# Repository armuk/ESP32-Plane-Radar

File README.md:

# Plane Radar

A live **ADS-B radar** on a round display: aircraft around your location with routes, aircraft details, local weather and time, settings in the browser, and signed over-the-air updates.

**Firmware:** [Releases](../../releases) · **3D printed case (STL + assembly):** [MakerWorld](https://makerworld.com/en/models/2872376-esp32-plane-radar-live-ads-b-on-a-round-display#profileId-3207083)

## Boards

Each board has its own folder, build and releases. **Flash only the files for your board.**

| Folder | Board | Status | Release tags and files |
|--------|-------|--------|------------------------|
| [`firmware/c3-supermini`](firmware/c3-supermini) | ESP32-C3 Super Mini + 1.28″ round GC9A01 (240×240) | **Released** | `v2.2.1`; files `plane-radar-v2.2.1-…`. These are the releases marked **Latest**. |
| [`firmware/s3`](firmware/s3) | ESP32-S3 with PSRAM (board to be chosen) | Port in progress, not usable yet | Will be `s3-v0.1.0`; files `plane-radar-s3-v0.1.0-…` |
| [`firmware/p4`](firmware/p4) | ESP32-P4 4″ round 720×720 touch (Waveshare ESP32-P4-WIFI6-Touch-LCD-4C) | Port in progress, not usable yet | Will be `p4-v0.1.0`; files `plane-radar-p4-v0.1.0-…` |
| [`firmware/cm4`](firmware/cm4) | Raspberry Pi CM4 or CM5 in an Echo Show 5 (2nd gen) case, 5.5″ 960×480 touch: radar plus Home Assistant dashboard | Hardware research, not usable yet | To be decided (not an ESP32 image) |

If you have a radar today, it is the **C3 Super Mini**: see its [README](firmware/c3-supermini/README.md) for wiring, setup, flashing and updates.

A file for a different chip (C3, S3 or P4) is refused: esptool, web flashers and the radar's own update all check the chip type. Before the S3 and P4 are released, their images will also carry a board marker, so a file for another board with the same chip is refused too. USB flashing the right file always recovers a radar.

## Building

Each folder is a separate PlatformIO project:

```bash
cd firmware/c3-supermini && pio run -e supermini
cd firmware/s3 && pio run -e s3
cd firmware/p4 && pio run -e p4
```

The S3 and P4 folders started as copies of the C3 firmware; their READMEs list what each port still needs. The [Build workflow](.github/workflows/build.yml) tests, checks and builds every board on each push; the [Release workflow](.github/workflows/release.yml) releases the C3 Super Mini from `v*` tags.

## Security, credits and licence

- [SECURITY.md](SECURITY.md): support period, reporting a vulnerability, network interfaces and the update signing key (written for the C3 Super Mini; the other boards will follow it).
- Origins and credits: this project builds on [ironicbadger/ESP32-Plane-Radar](https://github.com/ironicbadger/ESP32-Plane-Radar), a fork of [MatixYo/ESP32-Plane-Radar](https://github.com/MatixYo/ESP32-Plane-Radar). See the C3 README's [Origins and credits](firmware/c3-supermini/README.md#origins-and-credits).
- [LICENSE](LICENSE) (MIT).

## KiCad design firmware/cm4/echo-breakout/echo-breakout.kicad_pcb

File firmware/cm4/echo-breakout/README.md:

# Echo Show 5 breakout board (v2, drop-in)

A test board **the size and shape of the Echo's mainboard** (KC19-TI MLB, 108 × 60 mm). It screws into
the rear case in the mainboard's place, so every original ribbon plugs straight in. It's for mapping and
testing the Echo Show 5 (2nd gen, "cronos") parts before the CM4 carrier board is designed. See
[ECHO-SHOW-5.md](../ECHO-SHOW-5.md) for the hardware findings it serves.

## Why it's mainboard-shaped

The ribbons are short:

| Ribbon | Length | Note |
|---|---|---|
| Display (J44) | 17.5 mm | Tight |
| Touch (J30) | About 17.5 mm | Tight |
| Top board (J100) | 23 mm | |
| IO board (J46) | 44 mm | |

None of them can reach a board placed beside the Echo. So each socket sits where the original does, with
its ribbon-facing edge at the original's position. To work with the board outside the case, use the
[ribbon extenders](../ribbon-extenders/README.md). The positions were measured from two photos
(±0.3 mm across, ±0.8 mm down; see "Positions from the photos" in ECHO-SHOW-5.md).

## What's on it

| Socket | Part (LCSC) | Position (mm from the top-left corner) | Broken out to |
|---|---|---|---|
| **J44** display | Hirose FH26W-33S-0.3SHW(60) (C424654) | Body edge x = 4.2, centred y = 39.0, lock side left | P1, 2 × 17 |
| **J30** touch | Hirose FH34SRJ-8S-0.5SH(50) (C88372) | Front face x = 15.1, centred y = 53.8, opening left | P4, 1 × 8 |
| **J100** top board | HCTL HC-FPC-03-10-23RLTAG (C3012331), a copy of Hirose's FH26W-23S-0.3SHW | Body edge y = 4.5, centred x = 22.4, lock side up | P3, 2 × 12 |
| **J46** IO board | Hirose FH26W-31S-0.3SHW(60) (C2973806) | Body edge y = 4.4, centred x = 42.0, lock side up | P2, 2 × 16 |
| **J2** speaker | Molex Pico-SPOX 87438-0243 (C240853) | Centred x = 82.0, mating face 0.6 mm from the top edge, as on the mainboard | P8, 1 × 2 (top-right corner) |

How to read the headers:
- **Header pin n = Echo pin n** on every header, using the mainboard's own silkscreen pin 1:
  - J44 and J30: top end. On J30, 8 is at the bottom, nearest screw S4.
  - J100 and J46: right-hand end.
- The 2-row headers (J44, J100, J46) end with an extra GND pin.

**Mounting:**
- Six 2.6 mm plated holes at the original screw positions, assumed M2. The positions were measured
  from ruler photos of the mainboard (see "Measuring the screw holes" below). An M2 screw can sit up to
  0.3 mm off-centre in a 2.6 mm hole, and the screw head still covers it (the Echo's screws have 3.5 mm heads and are 5.1 mm long).
- **Each hole sits in an exposed, grounded copper pad** on both faces, as on the mainboard: 4.8 mm
  across (3.6 mm at S4, where the board edge is close). The screw head bears on the pad, not on
  solder mask, and the screw ties the board's ground to the case post.
- No tracks or vias within 2.6 mm of any hole centre on the outer layers (rule areas `SCREW_H1`–`H6`).
  The head reaches 1.9 mm out, or 2.2 mm with the screw fully off-centre.
- Screw S4 (bottom edge) is only 2.1 mm from the edge.
- **J44, J46 and J100 are Hirose FH26W sockets, the same way round as the mainboard's.** The ribbon
  enters on the lock side, which faces the board edge. Lift the lock, lay the ribbon in with its contacts
  as it sat in the Echo, and press the lock down onto it. The mainboard's J46 carries Hirose's mark on
  its lock and matches the FH26W-31 in size, leg counts (16 at the edge, 15 inboard) and end tabs.
- **J30 is a Hirose FH34SRJ-8S-0.5SH, at the mainboard socket's own position.** The mainboard's
  socket matches that part on every measured point: 6.0 mm wide, 3.8 mm deep, back-flip lock on the leg
  side, 0.3 mm ribbon, and a ribbon with 1.5 mm of bare contact and its insertion line at 1.5 mm.
  - An FH12 (used in earlier versions) doesn't work: it needs the ribbon 4.4 mm deep, and the Echo's
    touch ribbon has a 3 mm tongue of which 1.5 mm goes in.
  - The footprint is built in `gen_board.py` from Hirose's recommended pattern (FH34 catalogue, page 8,
    in `../parts-documentation/`): eight 0.3 × 0.8 mm lands and two 0.4 × 0.8 mm fitting lands.
  - **It's a back-flip socket: the lock lifts on the leg side, away from the ribbon.** Push the ribbon
    in to its white line, then press the lock down.
- **Bare ground pads.** The mainboard grounds to its surroundings through bare gold pads, and the
  breakout has the same ones. Keep them all bare: no tape, no flux residue.
  - **GP1, top, left of J30** (x 1.0–11.5, y 46.0–59.0): the touch ribbon lies across it. Four plated
    holes tie it to the ground pours on every layer.
  - **GP2, top-left corner** (x 0.6–9.0, y 0.6–4.8, with a sliver down the display edge to a second
    patch at y 12.4–14.0): the metal-mesh tape from the button/mic board sticks here.
  - **GB1–GB9, back:** nine pads where the display frame's conductive fabric gaskets press (GB2–GB5,
    GB7–GB9), plus GB1 under the J30 corner, where the GT911's ground pad rests, and GB6 on the
    display edge. No through-hole part sits inside any of them. Positions are in `BACK_PADS` in
    `gen_board.py`.
- **Two 2.5 mm alignment holes**, as on the mainboard, for the case's 1.8–1.9 mm locating pegs: A1 at 3.1, 16.8 (by the original's J45)
  and A2 at 93.4, 17.05 (by the original's part-number print). The mainboard's are about 2.5 mm.

**ESP32 section** (for the touch test, and for buttons, LEDs and ADC readings later):

- **U1A/U1B:** two 1 × 8 female sockets, 15.24 mm (0.6″) apart, for an **ESP32-C3 SuperMini**,
  component side up, with its USB-C pointing **left, into the board**. The case wall is too close to the
  right and bottom edges for a plug.
  - Pin order, both rows starting at the USB end:
    - Top row (U1A): 5V, GND, 3V3, 4, 3, 2, 1, 0.
    - Bottom row (U1B): 5, 6, 7, 8, 9, 10, 20, 21.
  - Pinout drawings of the module's underside show the rows the other way round.
  - Check the row spacing against your module before soldering the sockets.
  - Keep the area left of the module free of tall parts for the USB plug.
- **P6 EXT MCU:** 3V3, GND, the five control pins (IO4, IO5, IO6, IO7, IO10) and 5V. Wire any other
  ESP32 here instead.
- **P7 SPARE:** the remaining SuperMini pins. IO0–IO3 are ADC inputs, for the panel-ID resistor or supply
  checks.
- **Touch power switch:**
  - Q1 (AO3401A P-MOSFET) feeds 3V3 to `T_VDD`. IO4 low turns it on; R1 holds it off while the ESP32
    boots. D1 lights when it's on.
- **P5 TOUCH BUS:** V1, V2, GND, SDA, SCL, INT, RST.
  - V1 and V2 are both `T_VDD` (switched 3.3 V). On the Echo the touch side has two rails (3.0 V `vmch`
    and 3.3 V `vgp1`), so the second pin saves a Y-jumper.
  - The touch I/O voltage is still unknown. If a pin turns out to need 3.0 V, feed it from a bench
    supply instead of P5.
  - SDA, SCL, INT and RST come from IO5, IO6, IO7 and IO10 through 220 Ω series resistors (R3–R6).
  - SDA and SCL have 2.2 kΩ pull-ups (R7, R8) to `T_VDD`, so the pull-ups don't back-power the GT911
    when its supply is off. Each is connected by a shunt on **P9** (2 × 2 header: top row SDA,
    bottom row SCL). Pull a shunt off to remove that pull-up. JLCPCB fits the header, not the
    shunts: use two standard 2.54 mm jumper caps.
  - **Firmware rule:** while `T_VDD` is off (IO4 high), keep IO5, IO6, IO7 and IO10 low or
    high-impedance. Driving one high feeds the GT911 through its 220 Ω resistor.

The touch bus isn't wired to J30 on purpose. J30's signals aren't mapped yet, so once they are, connect
P5 to P4 with jumper wires. A wrong guess costs a wire, not a board.

## Marks on the board

Printed to help assembly and fault-finding:

- **Part names** beside every part and header (R1–R8, C1, C2, Q1, D1, J2, J30, J44, J46, J100,
  P1–P9), with the touch signals named at their resistors (`R3 SDA` … `R6 RST`) and pull-ups.
- **`RIBBON` with an arrow** on the entry side of each ribbon socket, and the end pin numbers (1 and 33,
  31, 23 or 8) at each socket's ends.
- **`! 12V ON J46 / P2: NO ECHO ADAPTER !`** on the front.
- **Which way round:** `CABLE EDGE`, `DISPLAY EDGE`, `FACE TO REAR CASE`, and for the ESP32 module
  `< USB`, `ANT >` and `COMPONENT SIDE UP`, with a line at each end of where the module sits.
- **Holes and pads:** S1–S6, A1, A2, and `KEEP BARE` by the bare ground pads.
- **Two white patches** to write pin functions on while mapping.
- **Back:** `CRONOS BREAKOUT BOARD V2` with `https://github.com/armuk` under it, the board's name, date
  and thickness in the notes, a `1` at pin 1 of every header for probing the solder
  side.
- **Three fiducials** (bare 1 mm dots, FID1–FID3) for the assembly machine.

## Measuring the screw holes

The hole positions come from two straight-down photos of the bare mainboard with a steel rule beside it
(2026-11-16). Each photo was perspective-corrected to the calipered outline (107.96 × 59.91 mm) and the
hole centres read off at full resolution. The two photos agree within 0.2 mm on every hole; the table is
in "Positions from the photos" in ECHO-SHOW-5.md.

To check a hole directly with calipers:

1. Lay the mainboard component side up, with the display edge (J44) on the left and the cable edge (J46,
   J100) at the top.
2. Measure from the left edge to the near side of the hole and to its far side; the average is the
   centre x. Do the same from the top edge for the centre y.
3. If a hole is more than 0.3 mm from the board's position, edit `SCREWS` in `gen_board.py` and rebuild.

## Using it

1. **Fitting:**
   - Take the old mainboard out.
   - Trim the through-hole pins flush on the back and cover **the pins** with Kapton tape. That side
     faces the display frame, as the mainboard's did. Leave the nine bare pads on the back uncovered:
     the frame's conductive gaskets press on them.
   - Stick the button/mic board's mesh tape to the bare pad in the top-left corner (GP2).
   - Screw the breakout in place and plug the ribbons in exactly as they went into the mainboard.
2. **Check pin 1 before trusting the labels.** Beep a pin you can identify (for example a wide ground
   trace) against the old mainboard.
3. **Map by continuity, unpowered.** Beep each header pin against the old mainboard's connector pins or
   test points.
4. **Touch test (the open fault):**
   1. Wire P5 to the J30 pins once they are mapped.
   2. Drive IO4 low to power the touch side, and hold RST low.
   3. Set INT low (0x5d) or high (0x14), then release RST.
   4. Scan I²C for 0x5d and 0x14. If the chip answers, read the product ID at 0x8140 and the sensor ID
      at 0x814A.
   5. **Never write the config registers (0x8047 onward).**
   6. Before switching the touch supply off (IO4 high), set IO5, IO6, IO7 and IO10 low or to inputs.
5. **Power:**
   - Power comes only from the ESP32's USB. The Echo's own 12 V supply comes in through the IO board
     and J46, so **never plug the Echo's adapter in while the breakout is fitted**.
   - J46's 12 V pins would then be live on P2.

## Ordering at JLCPCB

All order files are in [`jlcpcb/`](jlcpcb):

- `echo-breakout-gerbers.zip` (Gerbers and drill files)
- `bom.csv`
- `cpl.csv`

Steps:

1. Upload the zip. Settings:
   - **4 layers** (two layers couldn't fit the fan-out from the 0.3 mm sockets in the mainboard
     outline), **1.0 mm thick** like the mainboard (the ribbons wrap its edge, so a thicker board uses up
     ribbon length), JLC's default 4-layer stackup for that thickness.
   - 108 × 60 mm.
   - ENIG recommended (flatter pads for the 0.3 mm sockets).
   - Mark on PCB: **Remove Mark**. JLCPCB no longer prints the order number at a chosen spot (since May
     2026), so the board carries no `JLCJLCJLCJLC` marker.
2. Turn on **PCB Assembly**, top side, and upload the BOM and CPL.
   - **Edge rails and fiducials: let JLCPCB add them.** Parts sit as close as 0.3 mm to the board edge
     (J2, the ESP32 sockets, P8, the ribbon sockets), so the assembly line needs their 5 mm rails. The
     board's own three fiducials meet their rule (1 mm dot, 2 mm opening, over 3.35 mm from the edge).
   - Boards arrive with the rails attached unless you pay to have them removed. **Snap them off and
     file the break points flush** before fitting: the board has to drop into the mainboard's place.
3. **Check every part's rotation in JLCPCB's placement preview**, above all the four ribbon sockets:
   - Each socket's pin 1 mark must match the board.
   - **J44, J46 and J100 (FH26W):** the dark flip lock, the two metal end tabs and the larger leg row
     must be at the board edge, with the smaller leg row inboard. The ribbon enters on the lock side.
     Earlier versions of this board had them the other way round.
   - **J30 (FH34SRJ):** the opposite: its legs and lock are inboard, and the ribbon enters on the plain
     side facing the display edge.
   - **The placement file already carries JLCPCB's rotations** for the headers, the ESP32 sockets, the
     three FH26W-pattern sockets, Q1 and J2 (`JLC_ROTATION` in `finish_board.py`, read off their preview
     on 2026-11-16). In the preview, each part's magenta pin 1 mark must sit on the pad marked `1`, and
     its legs must lie on the pads.
   - **J30's and J2's footprints are this project's own**, so JLCPCB's rotation for them is the least
     certain. J30's eight legs must be on the right, away from the display edge. J2's two tails must
     point down the board, with its open mouth at the top edge.
4. **Three parts are substitutes**, as the first choices were out of stock at JLCPCB on 2026-11-16:

   | Part | First choice | In the BOM now |
   |---|---|---|
   | J100 | Hirose FH26W-23S-0.3SHW(60) (C3168948) | HCTL (Huacan Tianlu) HC-FPC-03-10-23RLTAG (C3012331) |
   | D1 | Everlight 19-217/GHC-YR1S2/3T (C72043) | NationStar NCD0603G1 (C84267), the same emerald green |
   | P1 | Kinghelm KH-2.54PH180-2X17P-L8.9 (C5157640) | Hong Cheng HC-PZ254-11.5L-2x17PZ (C41376108) |

   - **J100:** the copy's drawing matches the FH26W-23S: same signal lands, same ribbon (0.2 mm thick,
     7.2 mm wide, staggered), bottom contact, ribbon in on the tab side, 1.0 mm high. Only the tab lands
     differ, by 0.2 mm at most. Its flip lock is more fragile than Hirose's.
   - Two more copies with the same drawing: Hongcheng HC-FPC-0.3-23P-FH10 (C49166929) and
     XFCN F0302-B-23-10G-R (C25170829).
   - **P1, P2 and P3 are plain 11.5 mm pin headers**: Hong Cheng for P1 and P3 (P3:
     HC-PZ254-11.5L-2x12PZ, C41375953), HanElectricity 2541WV-2x16P (C25503139) for P2. Their pins
     stand 6 mm above the plastic, like the single-row headers. Two other 2 × 16 headers fit, but
     showed as a blank block in JLCPCB's preview: Hong Cheng HC-PZ254-11.5L-2x16PZ (C41376107) and
     Kinghelm KH-2.54PH180-2X16P-L11.5 (C19630944).
   - **Don't use Kinghelm's KH-2.54PH180-2XnP-L8.9 parts** (C5157640, C5157639, C5157635). They are
     shrouded IDC box headers, not plain pin headers: P2's and P3's bodies would collide.
   - To go back to a first choice, change its number in `gen_board.py` and rebuild.
5. **Through-hole parts are in the BOM too**, so JLCPCB fits the headers and the two ESP32 sockets
   (2.54 mm straight parts, Hong Cheng and Kinghelm):
   - This needs their through-hole assembly, which is priced per joint; there are about 150 joints.
   - Check each header's position and rotation in the placement preview. `cpl.csv` gives the centre of
     each part, which is what JLCPCB expects, but their library part may sit a quarter-turn off.
   - Stock on the less common sizes (2 × 12, 2 × 16, 2 × 17) is sometimes low. If one is short, mark
     it "do not place" and solder it yourself.
   - **The pins stand about 2 mm proud of the back.** Trim them flush before fitting the board in the
     Echo: the back faces the display frame and its conductive gaskets.
6. Left for you: the two GND test loops (TP1, TP2) are bare plated holes; solder in a wire loop or clip
   onto a screw pad instead.

DRC (KiCad 10): 0 unconnected items. No violations. The rules are 0.15 mm tracks and clearance, 0.4 mm power tracks and 0.3/0.6 mm
vias, and silkscreen strokes of at least 0.15 mm, all within JLCPCB's standard limits.

## Rebuilding

The board is generated by script. Run these from this folder; the autorouter is in the repo's
[`tools/`](../../../tools):

```bash
PY=/Applications/KiCad/KiCad.app/Contents/Frameworks/Python.framework/Versions/3.9/bin/python3
$PY gen_board.py          # placement, nets, silkscreen, BOM -> echo-breakout-unrouted.kicad_pcb + .dsn
java -Djava.awt.headless=true -jar ../../../tools/freerouting-2.1.0.jar --gui.enabled=false \
     -de "$PWD/echo-breakout.dsn" -do "$PWD/echo-breakout.ses" -mp 200 -mt 6
# check no net is missing from the session (Freerouting 2.1 can report success and still drop nets):
comm -13 <(grep -o '(net [^ )]*' echo-breakout.ses | sort -u) <(grep -o '(net [^ )]*' echo-breakout.dsn | sort -u)
$PY finish_board.py       # import routes, remove stubs, ground pours -> echo-breakout.kicad_pcb
kicad-cli pcb drc echo-breakout.kicad_pcb
sh make_jlcpcb.sh         # Gerbers, drill, CPL
```

**The committed `echo-breakout.ses` predates P9.** A fresh autoroute isn't needed for it: `finish_board.py`
lays the tracks around P9 itself (`route_pullups`), as it does for the speaker. A new session from
Freerouting works too.

Routing results vary between Freerouting runs. If the `comm` check lists any nets, run it again (a
different `-mt` thread count helps). Freerouting 2.1.0 runs on Java 21; the 2.5.0 macOS CLI build crashed
on this board. Editing the board by hand in KiCad is fine, but rerunning the scripts overwrites it.

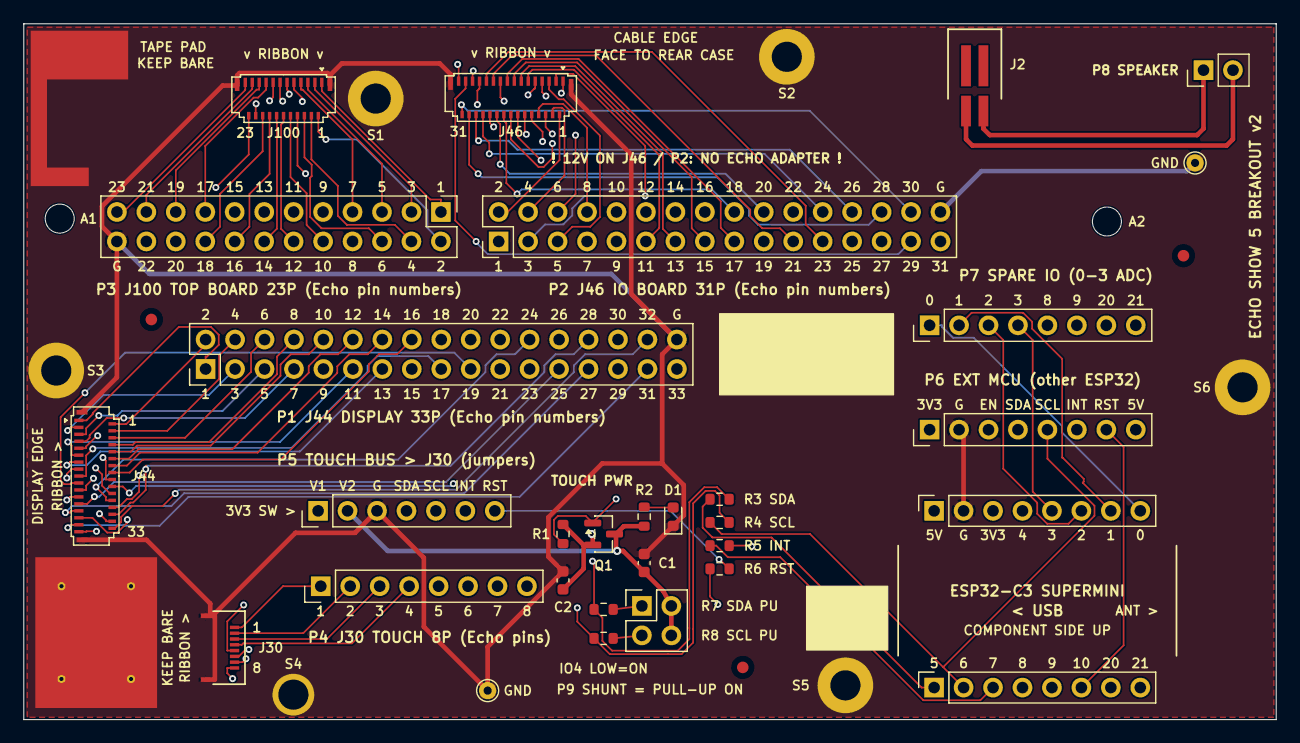
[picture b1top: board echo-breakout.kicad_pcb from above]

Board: 4 copper layers, 108.0 x 60.0 mm, 52 parts (0 on the bottom side), 121 nets.

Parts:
A1, A2: MountingHole_2.2mm_M2
C1, C2: 100nF; C_0603_1608Metric
D1: Green; LED_0603_1608Metric
FID1, FID2, FID3: Fiducial_1mm_Mask2mm
GB1, GB2, GB3, GB4, GB5, GB6, GB7, GB8, GB9: Ground pad; GroundPad
GP1: Touch ground pad; TouchGroundPad
GP2: Ground pad; GroundPad
H1, H2, H3, H4, H5, H6: MountingHole_2.2mm_M2
J2: 87438-0243; Molex_Pico-SPOX_87438-0243_1x02_P1.50mm_Horizontal
J30: FH34SRJ-8S-0.5SH(50); Hirose_FH34SRJ-8S-0.5SH_1x08-1MP_P0.50mm_Horizontal
J44: FH26W-33S-0.3SHW(60); Hirose_FH26-33S-0.3SHW_2Rows-33Pins-1MP_P0.60mm_Horizontal
J46: FH26W-31S-0.3SHW(60); Hirose_FH26-31S-0.3SHW_2Rows-31Pins-1MP_P0.60mm_Horizontal
J100: HC-FPC-03-10-23RLTAG; Hirose_FH26-23S-0.3SHW_2Rows-23Pins-1MP_P0.60mm_Horizontal
P1: PinHeader_2x17_P2.54mm_Vertical
P2: PinHeader_2x16_P2.54mm_Vertical
P3: PinHeader_2x12_P2.54mm_Vertical
P4, P6, P7: PinHeader_1x08_P2.54mm_Vertical
P5: PinHeader_1x07_P2.54mm_Vertical
P8: PinHeader_1x02_P2.54mm_Vertical
P9: PinHeader_2x02_P2.54mm_Vertical
Q1: AO3401A; SOT-23
R1: 10k; R_0603_1608Metric
R2: 1k; R_0603_1608Metric
R3, R4, R5, R6: 220R; R_0603_1608Metric
R7, R8: 2.2k; R_0603_1608Metric
TP1, TP2: TestPoint_THTPad_D1.5mm_Drill0.7mm
U1A, U1B: PinSocket_1x08_P2.54mm_Vertical

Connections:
+3V3: C2.1, P6.1, Q1.2, R1.2, U1A.3
+5V: P6.8, U1A.1
GND: C1.2, C2.2, D1.1, GB1.1, GB2.1, GB3.1, GB4.1, GB5.1, GB6.1, GB7.1, GB8.1, GB9.1, GP1.1, GP2.1, H1.1, H2.1, H3.1, H4.1, H5.1, H6.1, J30.MP, J44.MP, J46.MP, J100.MP, P1.34, P2.32, P3.24, P5.3, P6.2, TP1.1, TP2.1, U1A.2
IO0: P7.1, U1A.8
IO1: P7.2, U1A.7
IO2: P7.3, U1A.6
IO3: P7.4, U1A.5
IO4: P6.3, Q1.1, R1.1, U1A.4
IO5: P6.4, R3.1, U1B.1
IO6: P6.5, R4.1, U1B.2
IO7: P6.6, R5.1, U1B.3
IO8: P7.5, U1B.4
IO9: P7.6, U1B.5
IO10: P6.7, R6.1, U1B.6
IO20: P7.7, U1B.7
IO21: P7.8, U1B.8
J30_1: J30.8, P4.1
J30_2: J30.7, P4.2
J30_3: J30.6, P4.3
J30_4: J30.5, P4.4
J30_5: J30.4, P4.5
J30_6: J30.3, P4.6
J30_7: J30.2, P4.7
J30_8: J30.1, P4.8
J44_01: J44.1, P1.1
J44_02: J44.2, P1.2
J44_03: J44.3, P1.3
J44_04: J44.4, P1.4
J44_05: J44.5, P1.5
J44_06: J44.6, P1.6
J44_07: J44.7, P1.7
J44_08: J44.8, P1.8
J44_09: J44.9, P1.9
J44_10: J44.10, P1.10
J44_11: J44.11, P1.11
J44_12: J44.12, P1.12
J44_13: J44.13, P1.13
J44_14: J44.14, P1.14
J44_15: J44.15, P1.15
J44_16: J44.16, P1.16
J44_17: J44.17, P1.17
J44_18: J44.18, P1.18
J44_19: J44.19, P1.19
J44_20: J44.20, P1.20
J44_21: J44.21, P1.21
J44_22: J44.22, P1.22
J44_23: J44.23, P1.23
J44_24: J44.24, P1.24
J44_25: J44.25, P1.25
J44_26: J44.26, P1.26
J44_27: J44.27, P1.27
J44_28: J44.28, P1.28
J44_29: J44.29, P1.29
J44_30: J44.30, P1.30
J44_31: J44.31, P1.31
J44_32: J44.32, P1.32
J44_33: J44.33, P1.33
J46_01: J46.1, P2.1
J46_02: J46.2, P2.2
J46_03: J46.3, P2.3
J46_04: J46.4, P2.4
J46_05: J46.5, P2.5
J46_06: J46.6, P2.6
J46_07: J46.7, P2.7
J46_08: J46.8, P2.8
J46_09: J46.9, P2.9
J46_10: J46.10, P2.10
J46_11: J46.11, P2.11
J46_12: J46.12, P2.12
J46_13: J46.13, P2.13
J46_14: J46.14, P2.14
J46_15: J46.15, P2.15
J46_16: J46.16, P2.16
J46_17: J46.17, P2.17
J46_18: J46.18, P2.18
J46_19: J46.19, P2.19
J46_20: J46.20, P2.20
J46_21: J46.21, P2.21
J46_22: J46.22, P2.22
J46_23: J46.23, P2.23
J46_24: J46.24, P2.24
J46_25: J46.25, P2.25
J46_26: J46.26, P2.26
J46_27: J46.27, P2.27
J46_28: J46.28, P2.28
J46_29: J46.29, P2.29
J46_30: J46.30, P2.30
J46_31: J46.31, P2.31
J100_01: J100.1, P3.1
J100_02: J100.2, P3.2
J100_03: J100.3, P3.3
J100_04: J100.4, P3.4
J100_05: J100.5, P3.5
J100_06: J100.6, P3.6
J100_07: J100.7, P3.7
J100_08: J100.8, P3.8
J100_09: J100.9, P3.9
J100_10: J100.10, P3.10
J100_11: J100.11, P3.11
J100_12: J100.12, P3.12
J100_13: J100.13, P3.13
J100_14: J100.14, P3.14
J100_15: J100.15, P3.15
J100_16: J100.16, P3.16
J100_17: J100.17, P3.17
J100_18: J100.18, P3.18
J100_19: J100.19, P3.19
J100_20: J100.20, P3.20
J100_21: J100.21, P3.21
J100_22: J100.22, P3.22
J100_23: J100.23, P3.23
LED_A: D1.2, R2.2
PU_SCL: P9.3, R8.2
PU_SDA: P9.1, R7.2
SPK_1: J2.2, P8.1
SPK_2: J2.1, P8.2
T_INT: P5.6, R5.2
T_RST: P5.7, R6.2
T_SCL: P5.5, R4.2, R8.1
T_SDA: P5.4, R3.2, R7.1
T_VDD: C1.1, P5.1, P5.2, P9.2, P9.4, Q1.3, R2.1

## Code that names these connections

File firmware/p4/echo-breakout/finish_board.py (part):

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    ends = [xy(e) for t in board.GetTracks() if t.GetNetname() == 'T_VDD'
            for e in (t.GetStart(), t.GetEnd()) if near(e)]
    feed = min(ends, key=lambda e: (e[0] - pins['2'][0]) ** 2 + (e[1] - pins['2'][1]) ** 2) if ends else c1p
    routes = [('PU_SDA', 0.15, [xy(pos(r7, '2')), pins['1']]),
              ('PU_SCL', 0.15, [xy(pos(r8, '2')), pins['3']]),
              ('T_VDD', 0.4, [feed, pins['2'], pins['4']])]
    # The touch SDA and SCL tracks turned the corner below P9 where its pin 4 now is: turn them later.
    box = lambda v: 55.0 < pcbnew.ToMM(v.x) < 58.0 and 52.0 < pcbnew.ToMM(v.y) < 54.5
    for net, knee in (('T_SDA', 56.4), ('T_SCL', 56.72)):
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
